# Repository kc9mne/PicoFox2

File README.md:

Below is the orginal info from AI6YM I have modified the code to enable multiple audio files named audio1.wav though audio8.wav played in order on a cycle.

# PicoFox – A Hackable 2m Fox Transmitter

**PicoFox** is an open source fox transmitter for the 2-meter amateur band, built around the
RP2040 microcontroller (the same chip used in the Raspberry Pi Pico). It’s designed to be simple,
functional, and easy to modify.

PicoFox works well as a standalone fox for portable or walking hunts, but it’s also a great platform
for experimentation. There's ample CPU, flash, and GPIO available if you want to add features like
sensors or interactivity. The transmitter can generate a frequency or phase modulated signal with up
to 2.5kHz (data) bandwidth.

## Key Features
- Transmits FM in the 144–148 MHz band (ITU Zone 1: 144–146 MHz).
- Configured by editing a text file — no software or terminal needed.
- Transmits any 5kHz 16-bit PCM WAV file.
- Automatic Morse code ID with configurable tone, speed, and spacing.
- RF output > 12dBm / 15mW.
- Charges over USB.
- Expansion header provides:
  - 12 GPIOs (including I2C, SPI, UART, ADC).
  - Regulated 3.3V and raw battery voltage.
  - Two additional SI5351 clock outputs

### Getting One

Fully assembled PicoFox units are available from [AI6YM.radio](https://ai6ym.radio/picofox). An
enclosure, battery, and antenna are included. I ship nearly anywhere in the world.

You can also build your own - both the hardware and software are open source for non-commercial use.
For commercial inquiries, contact [justin@ai6ym.radio](mailto:justin@ai6ym.radio).

## Configuration

To configure your PicoFox, connect it to any computer using a micro USB cable. It will appear as a
USB mass storage device (like a flash drive). Open `settings.txt` with a text editor and adjust the
configuration values as needed. Eject the drive, disconnect USB, and power cycle the PicoFox to
apply the new settings.

To reset to factory settings, delete `settings.txt`, eject the drive, disconnect USB, and power
cycle the PicoFox. A default settings file will be regenerated.

### Settings Overview

- `CALLSIGN`: Alphanumeric callsign (max 12 characters).
- `ITU_ZONE`: ITU zone where the transmitter operates (`1`, `2`, or `3`).
- `FREQ_MHZ`: Transmit frequency in MHz.
- `DUTY_CYCLE`: Transmit duty cycle percentage (`0–100`).
- `MORSE_WPM`: Morse ID speed in words per minute.
- `MORSE_FARNSWORTH_WPM`: Slower Farnsworth spacing speed (ignored if lower than `MORSE_WPM`).
- `MORSE_TONE`: Morse tone frequency (100–2000 Hz).
- `MORSE_TONE_VOL`: Morse tone volume percentage (`1–100`).

**Note:** Invalid or missing values may disable the transmitter or revert to safe defaults.

## Using the Transmitter

After configuring settings as described above. The transmitter will turn on following the
provided settings the next time it is turned on.

The transmitter may be powered by an external USB power supply or the internal battery. The internal
battery charges over USB but no indication is available to show battery charging.

**Note: The power switch must be ON to charge the battery over USB. The transmitter will run on USB
power with the switch OFF but the battery will NOT be charged.**

A full battery will last about five hours at 100% duty cycle, 

## Replacing the Audio File

To change the audio transmission, replace the `audio.wav` file in the device’s flash storage. The
audio must be sampled at **5kHz**, **mono** (one channel), and encoded as **signed 16-bit PCM WAV**.

Using **Audacity** (free software available for all major OSs):

1. Set "Project Rate (Hz)" to `5000`.
2. Import, record, or generate your audio.
3. Mix down to a single mono track.
4. Export as WAV using **Signed 16-bit PCM** encoding.
5. Name the file `audio.wav` and copy it to the device.
6. Eject the drive and disconnect USB.
7. Power cycle the PicoFox.

**Notes:**

- Improper format may prevent audio transmission or cause noise to be transmitted instead.
- The audio is transmitted, followed by the morse ID, and then the transmitter turns off if
  `DUTY_CYCLE < 100`. In this way the length of the audio determines the transmit cycle time and the
  frequency of morse code ID transmissions. **YOU ARE RESPONSIBLE FOR COMPLYING WITH LOCAL LAWS FOR
  TRANSMITTING YOUR CALLSIGN!**
- To restore the default audio, delete `audio.wav`, eject the drive, disconnect USB, and power cycle
  the PicoFox.

## Design Brief

An SI5351 clock generator, locked to a TCXO, provides the RF signal. Modulation is applied in
software by the RP2040. To achieve smooth FM output, modulation is handled on core 1 with
I<sup>2</sup>C running at 1 MHz. Register writes are minimized and no other devices are on
I<sup>2</sup>C0.

Core 0 manages flash operations. Most extensions or new features should run on core 0.

**Note:** Mounting the device as a USB mass storage device will interrupt clean modulation as both
cores are blocked during flash operations.

The SPI flash device is split into program memory and a FAT16 filesystem. The filesystem contains
a text file for user-supplied settings, an audio file for transmission, a second audio file
containing the generated morse code ID, and a hash file used to detect changes to the settings file.
Unexpected files are automatically deleted and missing files are re-created from defaults in the
firmware binary.

The design intentionally includes large amounts of free CPU cycles, RAM, and flash so that cool
things can be built on the PicoFox.

## Development Guide

### Build Environment Setup

- Install Arduino IDE >= 2.3.
- Install libraries - Adafruit SPIFlash, Adafruit TinyUSB, Etherkit Si5351.
- Install board package from [my fork of Arduino-Pico](https://github.com/ai6ym/arduino-pico). This
  will be merged upstream eventually but for now you'll need the changes in my fork.
- In `Tools -> Board` select the `Raspberry Pi RP2040/RP2350 Boards -> AI6YM PicoFox`.
- Connect your PicoFox and select the appropriate TTY / COM port.

On Linux it may be necessary to add udev rules for this device. The relevant rules from my system
are below. I have no idea how this works on other operating systems. Mac is probably similar,
Windows should not be used for software developement of any kind (or really anything).

```
# Make an RP2040 in BOOTSEL mode writable by all users, so you can `picotool`
# without `sudo`. 
SUBSYSTEM=="usb", ATTRS{idVendor}=="2e8a", ATTRS{idProduct}=="0003", MODE="0666"

# Symlink an RP2040 running MicroPython from /dev/pico.
#
# Then you can `mpr connect $(realpath /dev/pico)`.
SUBSYSTEM=="tty", ATTRS{idVendor}=="2e8a", ATTRS{idProduct}=="0005", SYMLINK+="pico"

# Adafruit TinyUSB stack.
SUBSYSTEM=="tty", ATTRS{idVendor}=="239a", ATTRS{idProduct}=="cafe", MODE="0666"
SUBSYSTEM=="usb", ATTRS{idVendor}=="239a", ATTRS{idProduct}=="cafe", MODE="0666"
```

### Compilation Settings

- `Flash Size`: `16MB (Sketch: 1MB, FS: 15MB)`
- `CPU Speed`: `TBD`
- `USB Stack`: `Adafruit TinyUSB`

If needed for some reason you could change the partition layout to give more space for the sketch.
Doing so would destroy all data but the code automatically formats the partition and writes
defaults.

All other settings are fine at default values.

### Recovering a Board

In general the UF2 upload process will work fine. Click the upload button, after compilation the IDE
will push the board into UF2 update mode, write the new binary, and then reset the board to normal
operation.

If that doesn't work try the following:
- Reset the board and try again. Just tap the `RESET` button on the board to reset the RP2040.
- Force the device into `BOOTSEL` mode. Hold the `BOOTSEL` button, tap the `RESET` button, and then
  release the `BOOTSEL` button.
- Force the device into `BOOTSEL` mode **AND** change `Tools -> Upload Method` to `PicoTool`.
- When all else fails grab a PicoProbe (or a Pico / Pico2 flashed with the PicoProbe binary),
  connect that to the debug header of the PicoFox, and change `Tools -> Upload Method` to
  `Picoprobe`.
- If all of the above fails, well, he's dead Jim.

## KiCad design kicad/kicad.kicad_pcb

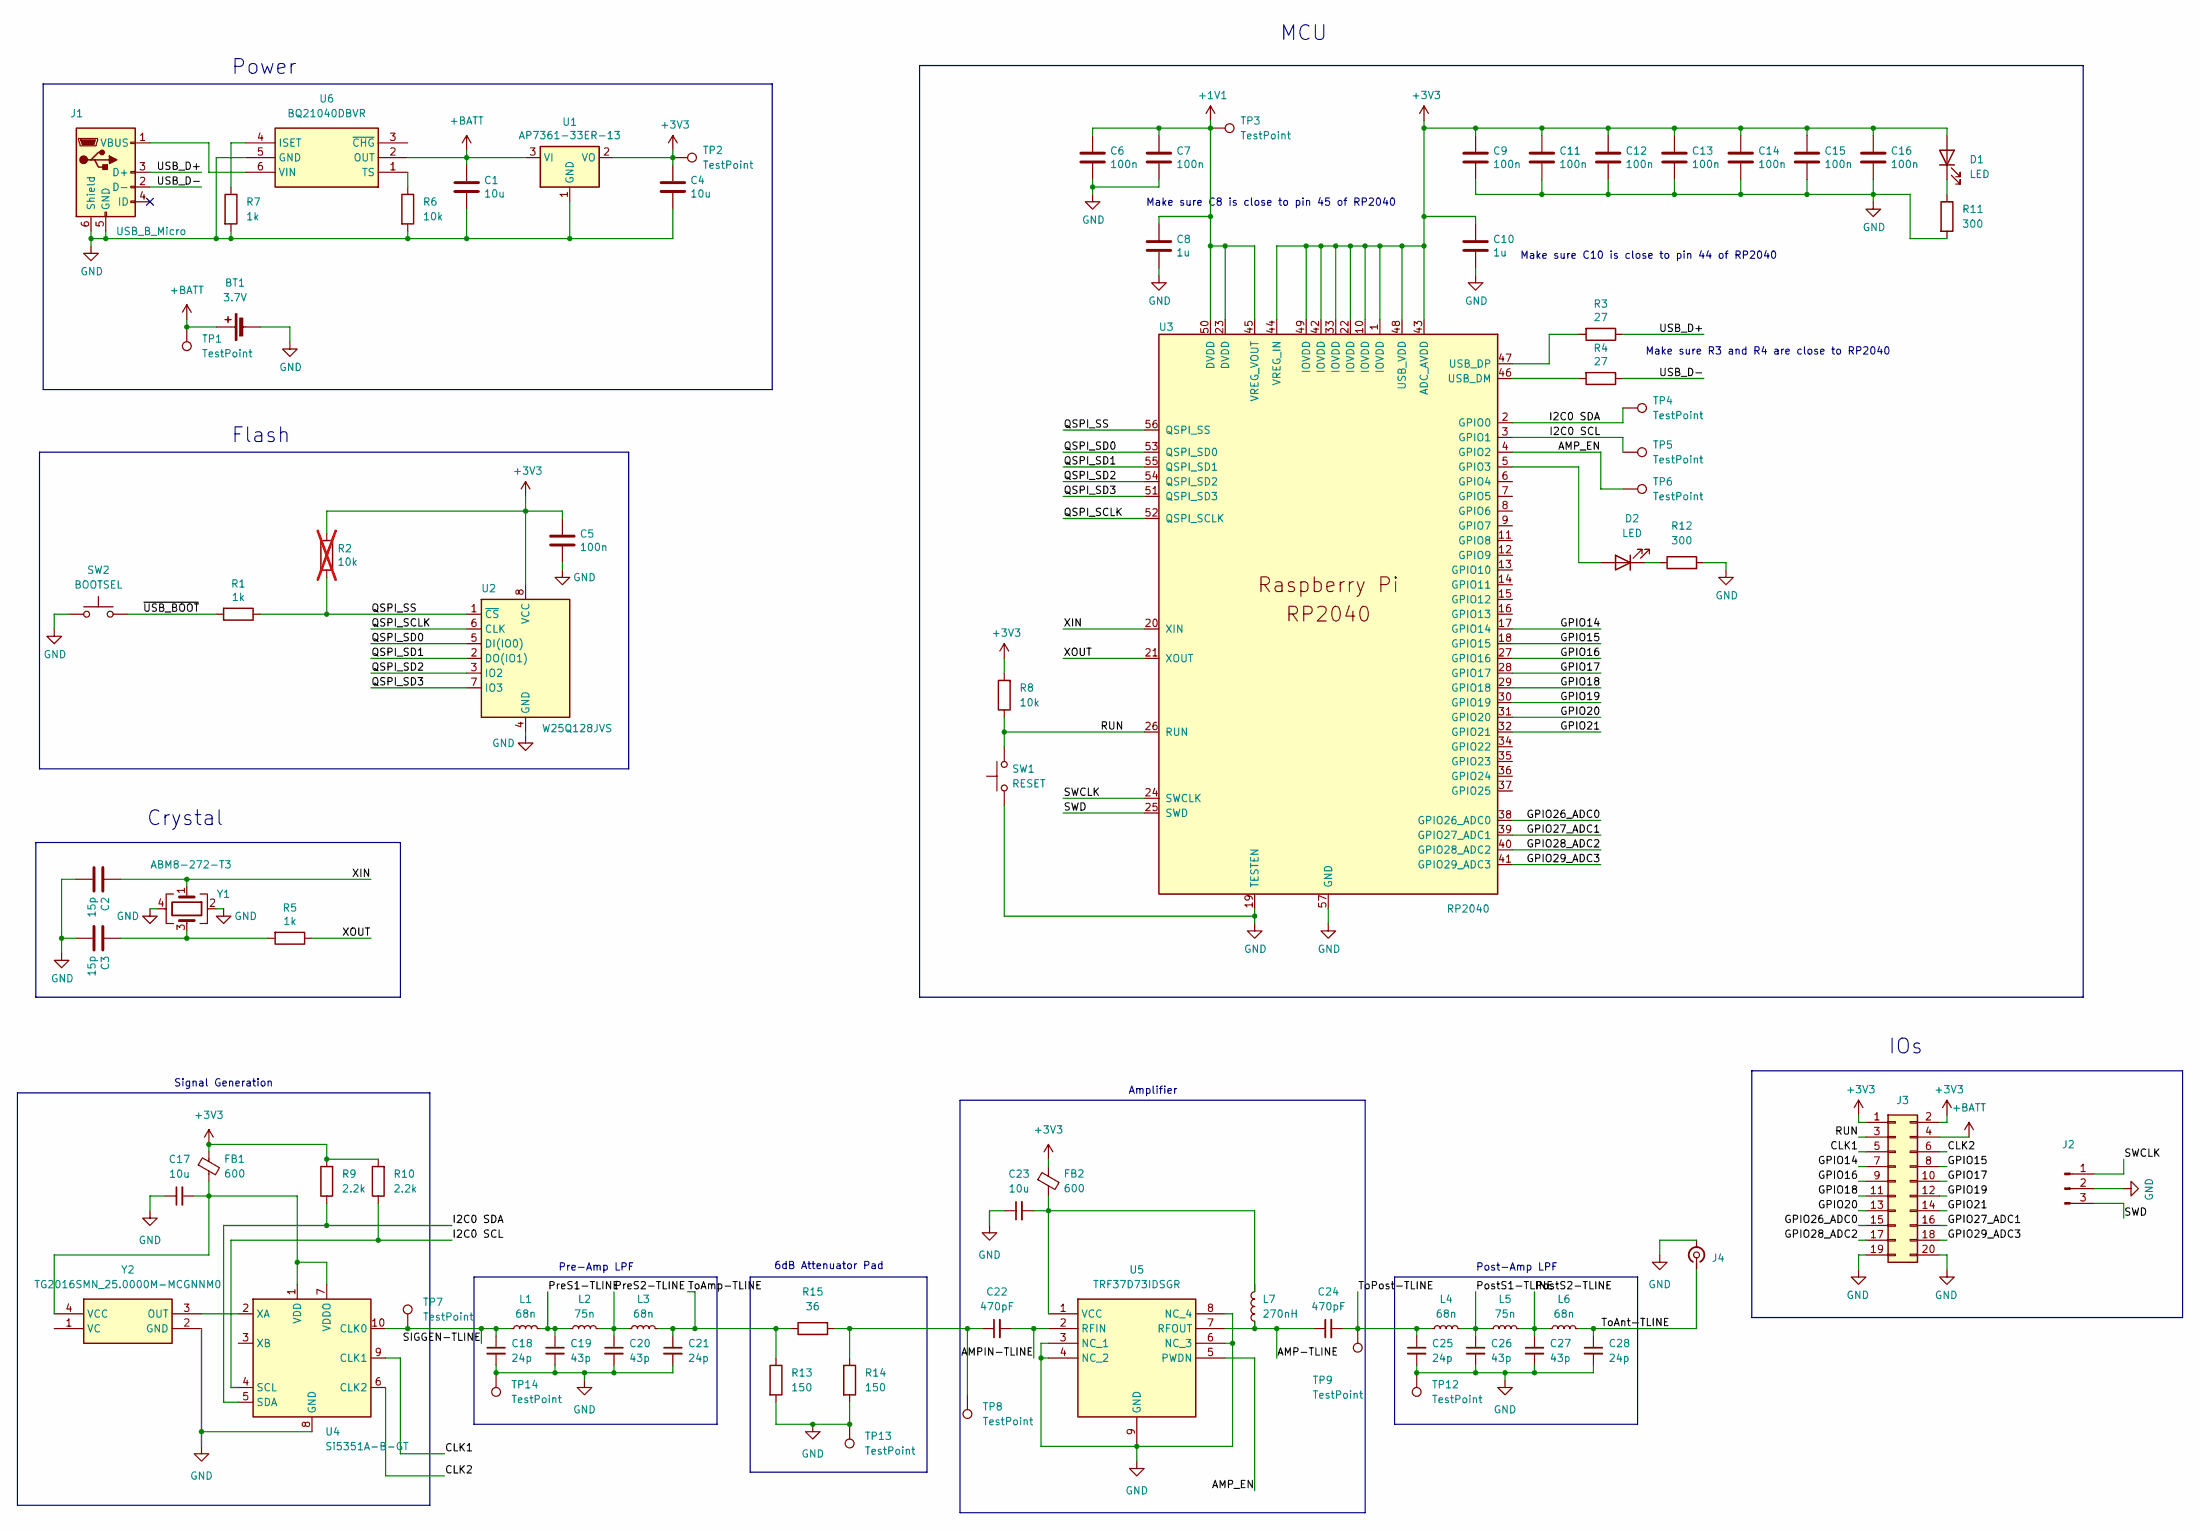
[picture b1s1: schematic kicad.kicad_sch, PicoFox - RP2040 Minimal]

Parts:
BT1: 3.7V; JST_PH_B2B-PH-K_1x02_P2.00mm_Vertical
C1, C4, C17, C23: 10u; C_0402_1005Metric
C2, C3: 15p; C_0402_1005Metric
C5, C6, C7, C9, C11, C12, C13, C14, C15, C16: 100n; C_0402_1005Metric
C8, C10: 1u; C_0402_1005Metric
C18, C21, C25, C28: 24p; C_0402_1005Metric
C19, C20, C26, C27: 43p; C_0402_1005Metric
C22, C24: 470pF; C_0402_1005Metric
D1, D2: LED; LED_0805_2012Metric
FB1, FB2: 600; L_0402_1005Metric
J1: USB_B_Micro; USB_Micro-B_Amphenol_10103594-0001LF_Horizontal_modified
J2: Conn_01x03_Pin; PinHeader_1x03_P2.54mm_Vertical
J3: Conn_02x10_Counter_Clockwise; PinHeader_2x10_P2.54mm_Vertical
J4: Conn_Coaxial_Small; SMA_Amphenol_901-143_Horizontal
L1, L3, L4, L6: 68n; L_0402_1005Metric
L2, L5: 75n; L_0402_1005Metric
L7: 270nH; L_0402_1005Metric
R1, R5, R7: 1k; R_0402_1005Metric
R2: 10k; R_0402_1005Metric; not fitted
R3, R4: 27; R_0402_1005Metric
R6, R8: 10k; R_0402_1005Metric
R9, R10: 2.2k; R_0402_1005Metric
R11, R12: 300; R_0402_1005Metric
R13, R14: 150; R_0402_1005Metric
R15: 36; R_0402_1005Metric
SW1: RESET; SW_Push_SPST_NO_Alps_SKRK
SW2: BOOTSEL; SW_Push_SPST_NO_Alps_SKRK
TP1, TP2, TP3, TP4, TP5, TP6, TP7, TP8, TP9, TP12, TP13, TP14: TestPoint; TestPoint_Pad_D1.0mm
U1: AP7361-33ER-13; SOT-223-3_TabPin2
U2: W25Q128JVS; SOIC-8_5.23x5.23mm_P1.27mm
U3: RP2040; RP2040-QFN-56
U4: Si5351A-B-GT; MSOP-10_3x3mm_P0.5mm
U5: TRF37D73IDSGR; WSON-8-1EP_2x2mm_P0.5mm_EP0.9x1.6mm; Mouser Part Number 595-TRF37D73IDSGR
U6: BQ21040DBVR; SOT95P280X145-6N; Mouser Part Number 595-BQ21040DBVR
Y1: ABM8-272-T3; Crystal_SMD_3225-4Pin_3.2x2.5mm
Y2: TG2016SMN_25.0000M-MCGNNM0; TG2016SMN250000MMCGNNM0; Mouser Part Number 732-2016SMN25MCGNNM0

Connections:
+1V1: C6.1, C7.1, C8.1, TP3.1, U3.23 (DVDD), U3.45 (VREG_VOUT), U3.50 (DVDD)
+3V3: C4.1, C5.1, C9.1, C10.1, C11.1, C12.1, C13.1, C14.1, C15.1, C16.1, D1.2 (A), FB1.1, FB2.1, J3.1, J3.2, R2.1, R8.2, R9.2, R10.2, TP2.1, U1.2 (VO), U2.8 (VCC), U3.1 (IOVDD), U3.10 (IOVDD), U3.22 (IOVDD), U3.33 (IOVDD), U3.42 (IOVDD), U3.43 (ADC_AVDD), U3.44 (VREG_IN), U3.48 (USB_VDD), U3.49 (IOVDD)
+BATT: BT1.1 (+), C1.1, J3.4, TP1.1, U1.3 (VI), U6.2 (OUT)
/AMP-TLINE: C24.1, L7.1, U5.7 (RFOUT); also elsewhere on the board
/AMPIN-TLINE: C22.2, U5.2 (RFIN)
/AMP_EN: TP6.1, U3.4 (GPIO2), U5.5 (PWDN)
/CLK1: J3.5, U4.9 (CLK1)
/CLK2: J3.6, U4.6 (CLK2)
/GPIO14: J3.7, U3.17 (GPIO14)
/GPIO15: J3.8, U3.18 (GPIO15)
/GPIO16: J3.9, U3.27 (GPIO16)
/GPIO17: J3.10, U3.28 (GPIO17)
/GPIO18: J3.11, U3.29 (GPIO18)
/GPIO19: J3.12, U3.30 (GPIO19)
/GPIO20: J3.13, U3.31 (GPIO20)
/GPIO21: J3.14, U3.32 (GPIO21)
/GPIO26_ADC0: J3.15, U3.38 (GPIO26_ADC0)
/GPIO27_ADC1: J3.16, U3.39 (GPIO27_ADC1)
/GPIO28_ADC2: J3.17, U3.40 (GPIO28_ADC2)
/GPIO29_ADC3: J3.18, U3.41 (GPIO29_ADC3)
/I2C0 SCL: R10.1, TP5.1, U3.3 (GPIO1), U4.4 (SCL)
/I2C0 SDA: R9.1, TP4.1, U3.2 (GPIO0), U4.5 (SDA)
/PostS1-TLINE: C26.1, L4.2, L5.1
/PostS2-TLINE: C27.1, L5.2, L6.1
/PreS1-TLINE: C19.1, L1.2, L2.1
/PreS2-TLINE: C20.1, L2.2, L3.1
/QSPI_SCLK: U2.6 (CLK), U3.52 (QSPI_SCLK)
/QSPI_SD0: U2.5 (DI(IO0)), U3.53 (QSPI_SD0)
/QSPI_SD1: U2.2 (DO(IO1)), U3.55 (QSPI_SD1)
/QSPI_SD2: U2.3 (IO2), U3.54 (QSPI_SD2)
/QSPI_SD3: U2.7 (IO3), U3.51 (QSPI_SD3)
/QSPI_SS: R1.1, R2.2, U2.1 (~CS), U3.56 (QSPI_SS)
/RUN: J3.3, R8.1, SW1.2, U3.26 (RUN)
/SIGGEN-TLINE: C18.1, L1.1, TP7.1, U4.10 (CLK0)
/SWCLK: J2.1, U3.24 (SWCLK)
/SWD: J2.3, U3.25 (SWD)
/ToAmp-TLINE: C21.1, L3.2, R13.1, R15.1
/ToAnt-TLINE: C28.1, J4.1 (In), L6.2
/ToPost-TLINE: C24.2, C25.1, L4.1, TP9.1
/USB_D+: J1.3 (D+), R3.1
/USB_D-: J1.2 (D-), R4.1
/XIN: C2.1, U3.20 (XIN), Y1.1
/XOUT: R5.1, U3.21 (XOUT)
/~USB_BOOT: R1.2, SW2.2
GND: BT1.2 (-), C1.2, C2.2, C3.2, C4.2, C5.2, C6.2, C7.2, C8.2, C9.2, C10.2, C11.2, C12.2, C13.2, C14.2, C15.2, C16.2, C17.1, C18.2, C19.2, C20.2, C21.2, C23.1, C25.2, C26.2, C27.2, C28.2, J1.5 (GND), J1.6 (Shield), J2.2, J3.19, J3.20, J4.2 (Ext), R6.2, R7.2, R11.2, R12.2, R13.2, R14.2, SW1.1, SW2.1, TP12.1, TP13.1, TP14.1, U1.1 (GND), U2.4 (GND), U3.19 (TESTEN), U3.57 (GND), U4.8 (GND), U5.3 (NC_1), U5.4 (NC_2), U5.6 (NC_3), U5.8 (NC_4), U5.9 (GND), U6.5 (GND), Y1.2, Y1.4, Y2.2 (GND)
unnamed: C3.1, R5.2, Y1.3
unnamed: C22.1, R14.1, R15.2, TP8.1
unnamed: D1.1 (K), R11.1
unnamed: D2.2 (A), U3.5 (GPIO3)
unnamed: D2.1 (K), R12.1
unnamed: J1.1 (VBUS), U6.6 (VIN)
unnamed: R4.2, U3.46 (USB_DM)
unnamed: R3.2, U3.47 (USB_DP)
unnamed: C17.2, FB1.2, U4.1 (VDD), U4.7 (VDDO), Y2.4 (VCC)
unnamed: U4.2 (XA), Y2.3 (OUT)
unnamed 55: C23.2, FB2.2, U5.1 (VCC); also elsewhere on the board
unnamed: R7.1, U6.4 (ISET)
unnamed: R6.1, U6.1 (TS)

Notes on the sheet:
IOs
Power
Amplifier
Make sure C8 is close to pin 45 of RP2040
Crystal
Pre-Amp LPF
Make sure C10 is close to pin 44 of RP2040
Post-Amp LPF
Signal Generation
Make sure R3 and R4 are close to RP2040
Flash
6dB Attenuator Pad
MCU

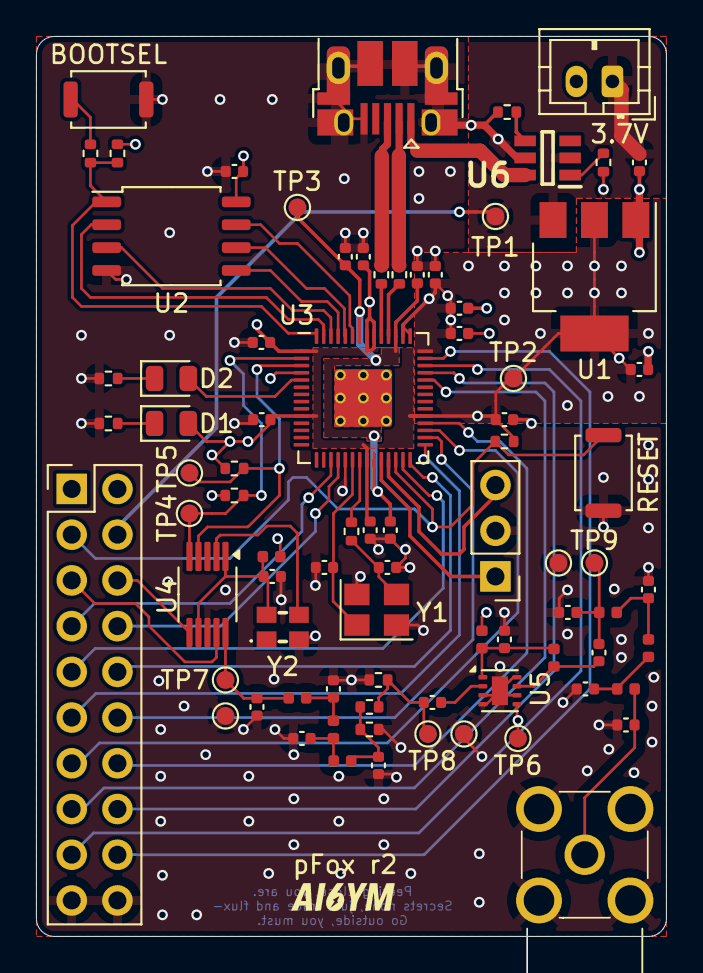
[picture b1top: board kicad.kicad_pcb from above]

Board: 4 copper layers, 35.0 x 50.0 mm, 81 parts (0 on the bottom side), 58 nets.

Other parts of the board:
FB3: 600; L_0402_1005Metric

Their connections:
/AMP-TLINE: FB3.1; also elsewhere on the board
unnamed 55: FB3.2; also elsewhere on the board

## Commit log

2025-07-16 Initial commit, PicoFox r2.
2025-09-12 Added enclosure STLs.
2025-10-30 Update firmware.ino
    Modify code to enable multiple sequenced playback of audio files.
2025-11-02 Update firmware.ino
    Added sequential playback of 11 files in a row and tweaked the audio.
